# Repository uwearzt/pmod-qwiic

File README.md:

# Adapter PMOD to Quiic

A small Adapter to directly attach Quiic Sensors from Sparkfun to FPGA, or
other Boards with PMOD Connector.

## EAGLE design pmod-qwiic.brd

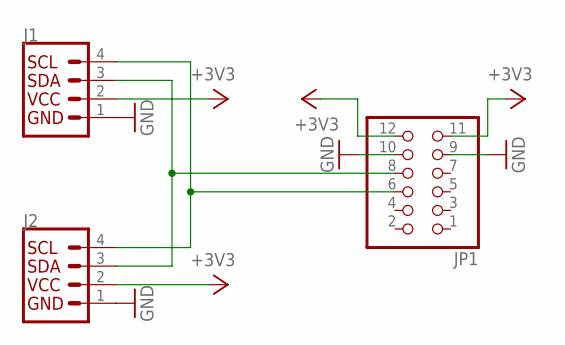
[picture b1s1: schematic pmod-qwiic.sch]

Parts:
J1, J2: QWIIC_CONNECTORJS-1MM; 1X04_1MM_RA
JP1: PINHD-2X6/90; 2X06/90

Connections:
+3V3: J1.2 (VCC), J2.2 (VCC), JP1.11, JP1.12
GND: J1.1 (GND), J2.1 (GND), JP1.9, JP1.10
unnamed: J1.3 (SDA), J2.3 (SDA), JP1.8
unnamed: J1.4 (SCL), J2.4 (SCL), JP1.6

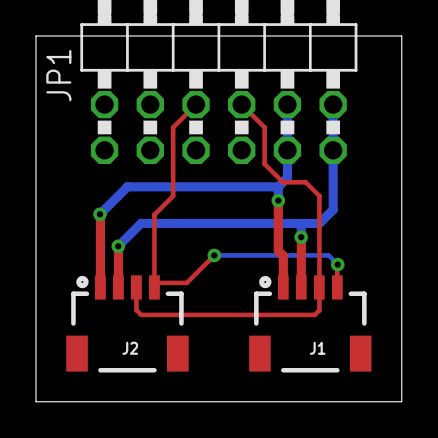
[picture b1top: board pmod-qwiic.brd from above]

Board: 2 copper layers, 20.3 x 20.3 mm, 3 parts (0 on the bottom side), 4 nets.

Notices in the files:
parts and their libraries:
SparkFun-Connectors: Licensing: Creative Commons ShareAlike 4.0 International - https://creativecommons.org/licenses/by-sa/4.0
